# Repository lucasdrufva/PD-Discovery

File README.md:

# PD-Discovery

<div>
  
</div>

A tool for analyzing and discovering the Power Delivery Protocol for USB-C

[Demo Video](https://youtu.be/lnGGlh1nLXM)

Capable of 
 - Requesting identity from electronically marked cables, displaying supported Amp rating and length of cable
 - Displaying source capabilities including the different voltage and current ratings
 - Requesting power from a source and providing it on a screw terminal 
 - Displaying sink capabilities including the different voltage and current ratings
 - Providing power from internal battery to answer source request
 - Charge internal battery by requesting 5 Volt

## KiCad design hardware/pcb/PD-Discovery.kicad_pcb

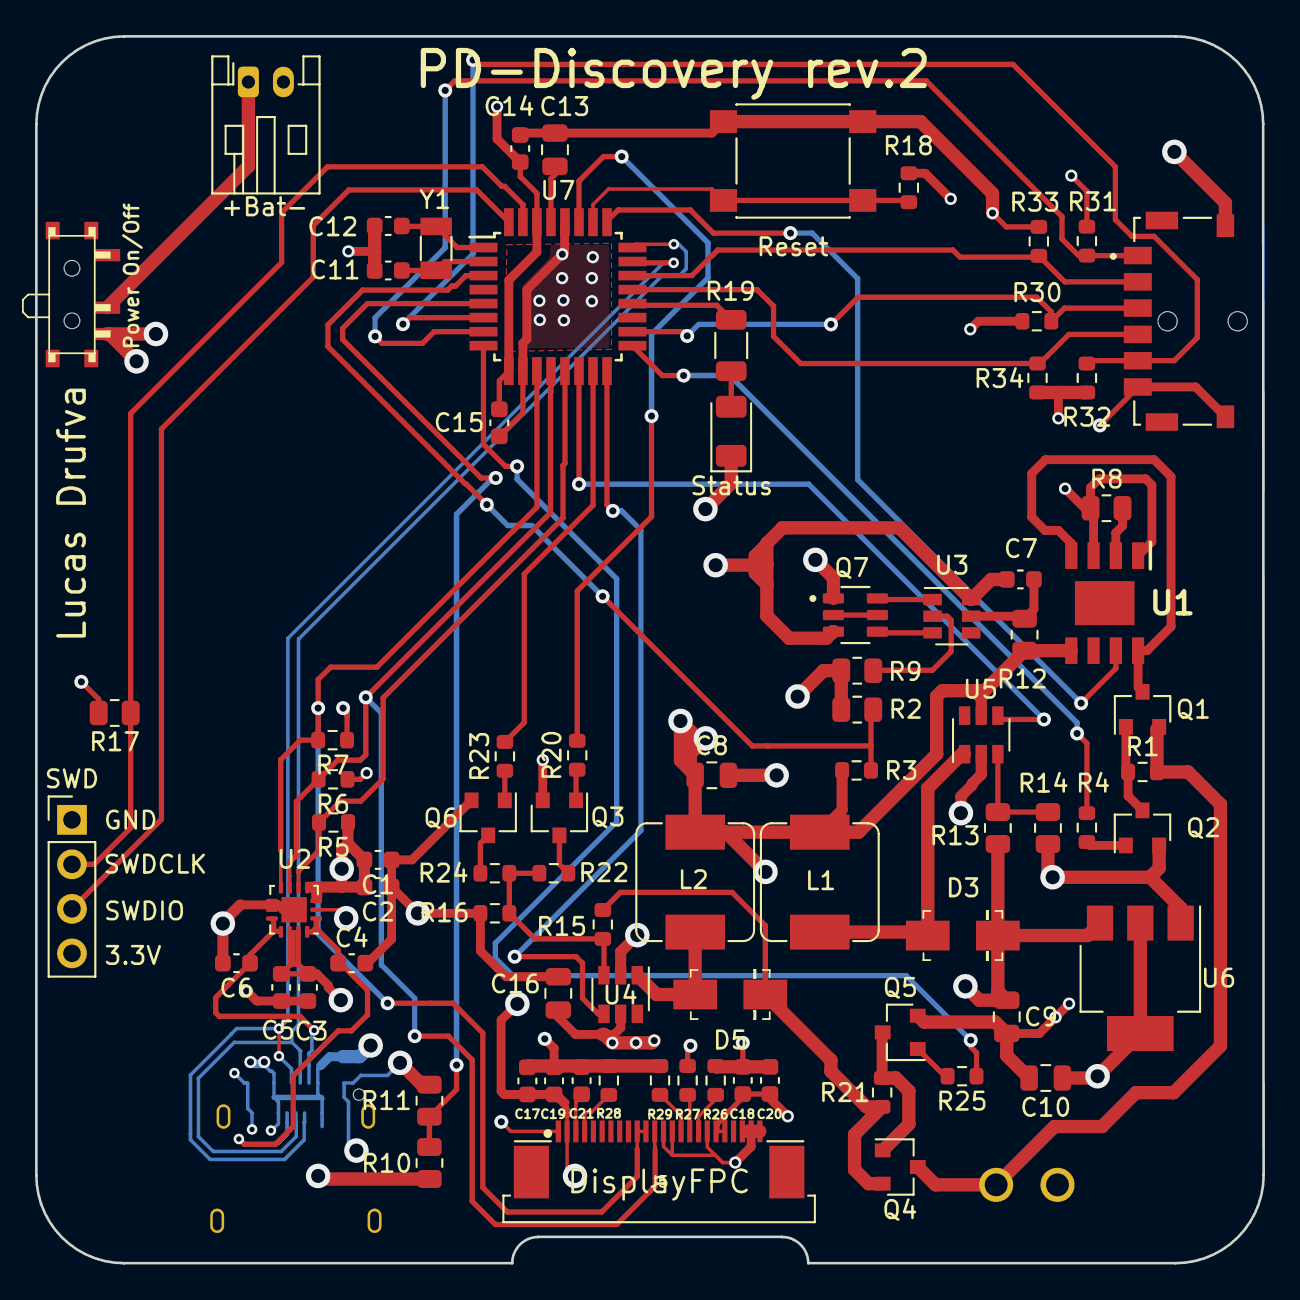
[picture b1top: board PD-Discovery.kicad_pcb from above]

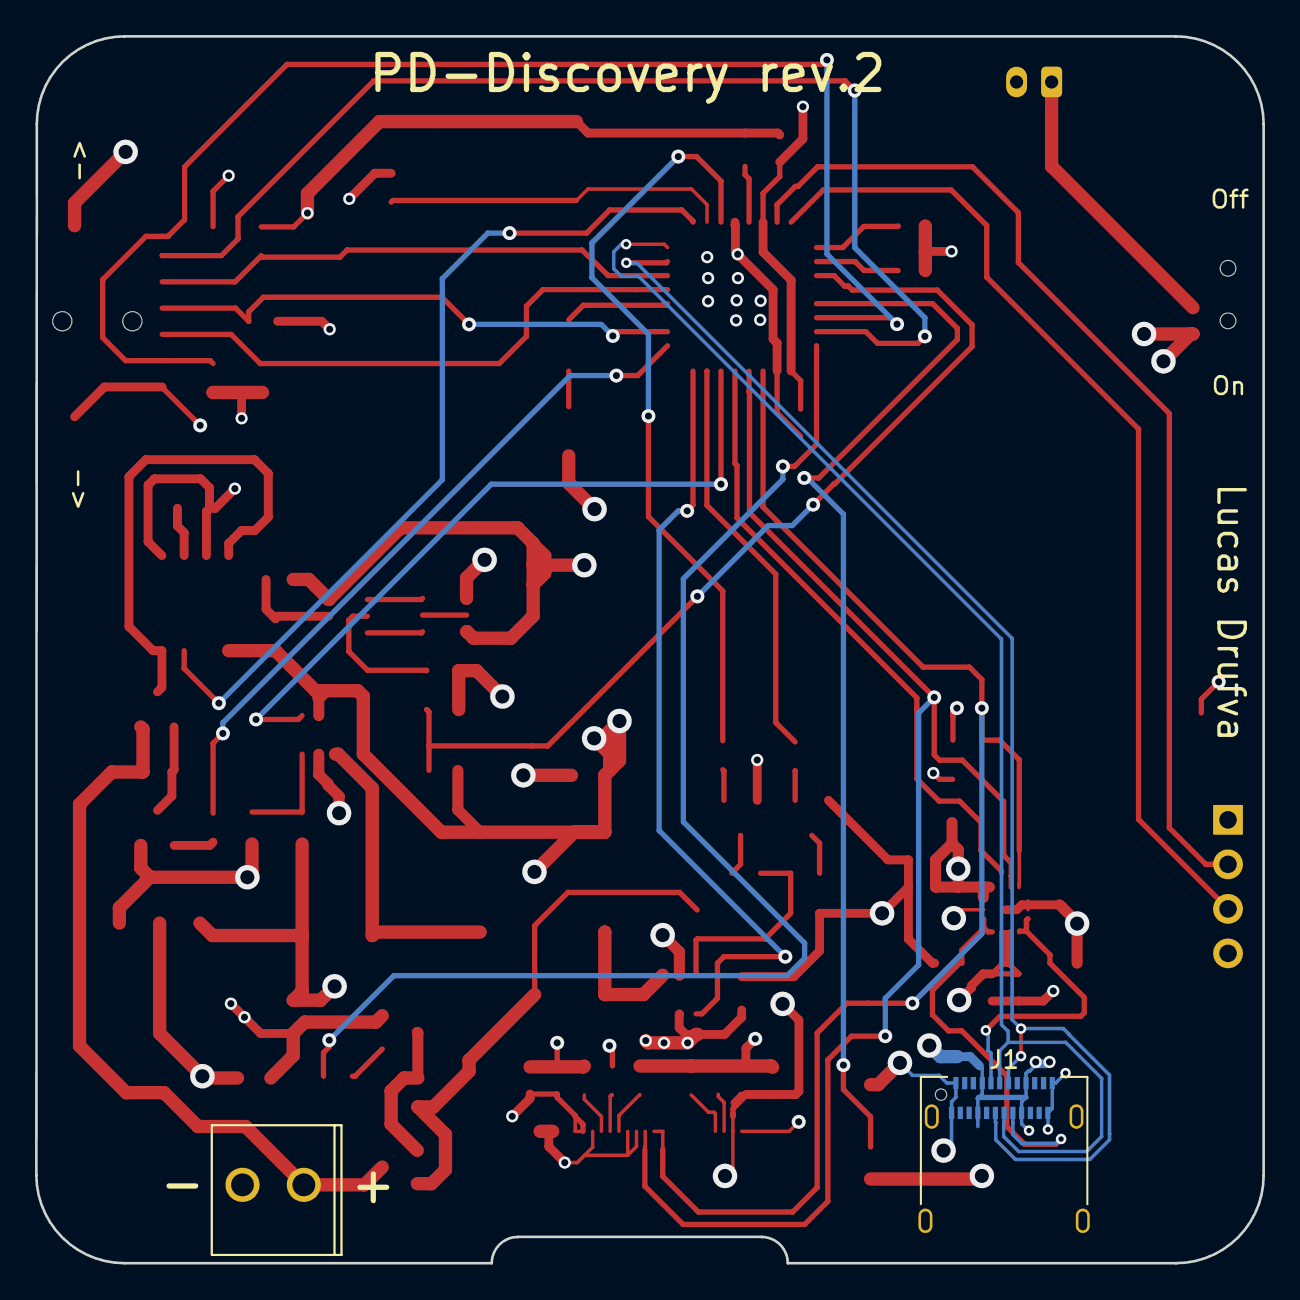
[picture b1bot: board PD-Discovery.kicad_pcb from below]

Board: 4 copper layers, 70.0 x 70.0 mm, 83 parts (2 on the bottom side), 61 nets.

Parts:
+Bat-: Battery; JST_PH_S2B-PH-K_1x02_P2.00mm_Horizontal
C1, C3, C7, C17, C18: 0.1uF; C_0603_1608Metric
C2, C5, C14, C15, C19: 10uF; C_0603_1608Metric
C4, C6: 470pF; C_0603_1608Metric
C8, C9, C10, C16: 22uF; C_0805_2012Metric
C11, C12: 16pF; C_0603_1608Metric
C13: 1uF; C_0805_2012Metric
C20, C21: 4.7uF; C_0603_1608Metric
D3, D5: D_Schottky; DO-214AC
J1: USB_C_Receptacle; USB_C_Receptacle_Amphenol_12401610E4-2A
J4: ScrewTerminal; 691214110002
J5: DisplayFPC; ER-CON24HT-1
L1, L2: 22uH; L_Sumida_CDMC6D28_7.25x6.5mm
Power On/Off: SSSS810701
Q1, Q4: AO3401A; SOT-23
Q2, Q3, Q5, Q6: BC817; SOT-23
Q7: FS8205; SOT95P280X145-6N
R1, R15, R18, R21, R26, R27, R29, R30, R31, R32, R33, R34: 10K; R_0603_1608Metric
R2, R10: 1M; R_0805_2012Metric
R3: 523K; R_0603_1608Metric
R4, R20, R23, R25: 5K; R_0603_1608Metric
R5, R6, R7: 4.7K; R_0603_1608Metric
R8: 3K; R_0805_2012Metric
R9, R14, R17: 1K; R_0805_2012Metric
R11: 150K; R_0805_2012Metric
R12: 100; R_0805_2012Metric
R13: 7.5K; R_0805_2012Metric
R16: 1.35K; R_0603_1608Metric
R19: 220; R_1206_3216Metric
R22: 1.5K; R_0603_1608Metric
R24: 2K; R_0603_1608Metric
R28: 900K; R_0603_1608Metric
Reset: SW_Push; SW_Push_1P1T_NO_6x6mm_H9.5mm
S1: SLLB120300; SW_SLLB120300
SWD: SWD; PinHeader_1x04_P2.54mm_Vertical
Status: LED; LED_1206_3216Metric
U1: TP4056; SOIC127P600X175-9N
U2: FUSB302BMPX; WQFN-14-1EP_2.5x2.5mm_P0.5mm_EP1.45x1.45mm
U3: DW01; SOT-23-6
U4, U5: MT3608; SOT-23-6
U6: AMS1117-3.3; SOT-223-3_TabPin2
U7: ATSAMD21E18A-A; TQFP-32_7x7mm_P0.8mm
Y1: Crystal; Crystal_SMD_3215-2Pin_3.2x1.5mm

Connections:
+3V3: C1.2, C2.2, C10.1, C14.2, C15.2, C18.1, C20.1, J5.19, J5.20, R5.1, R6.1, R7.1, R17.2, R18.1, R27.2, S1.C_1, S1.C_2, SWD.4, U2.3, U2.4, U6.2, U7.9, U7.30
/XIN32: C12.2, U7.1, Y1.1
/XOUT32: C11.2, U7.2, Y1.2
/boostFB: R15.2, R16.1, R22.1, R24.1, U4.3
/boostSW: D5.A, L2.2, U4.1
/reset: R18.2, Reset.2, U7.26
BAT+: C8.1, C16.1, L1.1, L2.1, Power On/Off.3, R3.1, R12.1, U1.5, U4.5, U5.5
BAT-: +Bat-.2, C7.2, Q7.3, U3.6
CC1: C6.1, J1.A5, U2.10, U2.11
CC2: C4.1, J1.B5, U2.1, U2.14
CHRG: U1.7, U7.25
D+: J1.A6, J1.B6, U7.24
D-: J1.A7, J1.B7, U7.23
En9V: R20.2, U7.27
En12V: R23.2, U7.15
EnCharger: R4.1, U7.17
EnOut: R25.1, U7.8
EnOutSrc: U4.4, U7.16
EnVconn: U5.4, U7.14
GND: C1.1, C2.1, C3.1, C4.2, C5.1, C6.2, C8.2, C9.2, C10.2, C11.1, C12.1, C13.2, C14.1, C15.1, C16.2, C17.2, C18.2, C19.2, C20.2, C21.2, J1.A1, J1.A12, J1.B1, J1.B12, J4.2, J5.1, J5.13, J5.14, J5.18, J5.22, J5.23, J5.24, Q2.2, Q3.2, Q5.2, Q6.2, Q7.1, R2.1, R8.1, R9.2, R11.2, R14.2, R16.2, R26.2, R28.1, R29.2, R30.2, R31.1, R32.2, R33.1, R34.2, Reset.1, S1.GND, SWD.1, Status.1, U1.1, U1.3, U2.8, U2.9, U2.15, U4.2, U5.2, U6.1, U7.10, U7.28
INT: R5.2, U2.5, U7.13
MeasBat: R2.2, R3.2, U7.3
MeasVBus: R10.2, R11.1, U7.5
unnamed: C7.1, R12.2, U3.5
unnamed: C13.1, U7.29
unnamed: C21.1, J5.3
unnamed: D3.A, L1.2, U5.1
unnamed: R19.2, Status.2
unnamed: D5.K, Q4.2, R15.1, R21.1
unnamed: J5.4, R28.2
unnamed: J5.15, R29.1
unnamed: J5.16, R27.1
unnamed: J5.17, R26.1
unnamed: Q1.1, Q2.3, R1.1
unnamed: Q1.3, U1.4, U1.8
unnamed: Q2.1, R4.2
unnamed: Q3.1, R20.1
unnamed: Q3.3, R22.2
unnamed: Q4.1, Q5.3, R21.2
unnamed: Q5.1, R25.2
unnamed: Q6.1, R23.1
unnamed: Q6.3, R24.2
unnamed: Q7.2, Q7.5
unnamed: Q7.4, U3.3
unnamed: Q7.6, U3.1
unnamed: R8.2, U1.2
unnamed: R9.1, U3.2
unnamed: R13.2, R14.1, U5.3
unnamed: R19.1, U7.20
RawBAT+: +Bat-.1, Power On/Off.2
SCL: J5.12, R6.2, U2.6, U7.12
SDA: J5.10, J5.11, R7.2, U2.7, U7.11
SWDCLK: R17.1, SWD.2, U7.31
SWDIO: SWD.3, U7.32
VBus: J1.A4, J1.A9, J1.B4, J1.B9, J4.1, Q1.2, Q4.3, R1.2, R10.1, U2.2
Vconn: C3.2, C5.2, C9.1, C17.1, C19.1, D3.K, J5.2, R13.1, U2.12, U2.13, U6.3
down1: R34.1, S1.3, U7.21
down2: R32.1, S1.4, U7.6
select: R30.1, S1.T, U7.18
up1: R33.2, S1.2, U7.22
up2: R31.2, S1.1, U7.7

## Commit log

2022-04-27 not working
2022-05-04 Start of rev2
2022-05-04 Menu system
2022-05-26 Working release
2022-05-29 Added hardware
2022-06-05 Request pdo from source
2022-06-07 Removed USB-PD & fusb302 to replace with submodule
2022-06-07 Added USB-PD as submodule
2022-06-07 Bumped USB-PD
